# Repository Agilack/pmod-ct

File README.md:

PMOD Current Transformer
========================

This PMOD allow to interface a current transformer (CT) for current measurement
with no direct electrical coupling. This PMOD use a type 2 (SPI) port to
control the embedded 12 bits analog to digital converter.

CAD source
----------

This board has been designed using KiCad EDA (version 5). All sources files
(schematics, routing, ...) are available into the `prj-kicad` folder. You can
re-use this design under terms of the Creative Commons ShareAlike license
(CC BY-SA)

<table>
<tr>
<td></td>
<td></td>
</tr>
<tr>
<td>Fig1: Preview of the KiCad schematics</td>
<td>Fig2: Preview of the KiCad routing</td>
</tr>
</table>

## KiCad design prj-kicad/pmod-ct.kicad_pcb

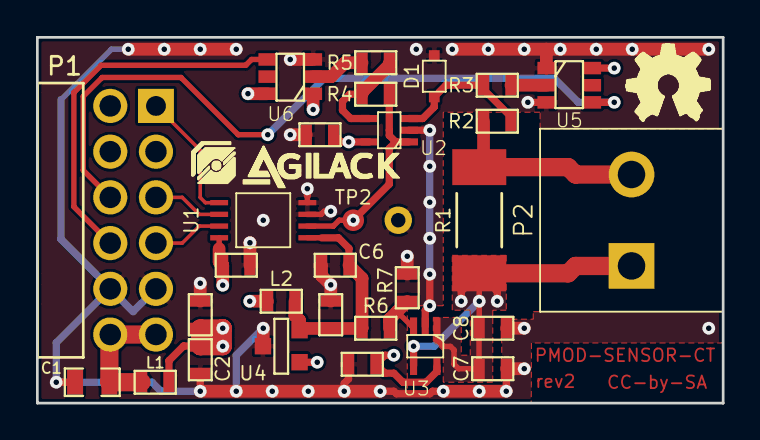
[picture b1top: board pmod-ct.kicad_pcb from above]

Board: 4 copper layers, 38.1 x 20.3 mm, 32 parts (0 on the bottom side), 17 nets.

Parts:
C1: 10uF; SMD0805
C2: 1uF; SMD0603
C3, C6, C8: 470pF; SMD0603
C4, C5, C9, C10: 100nF; SMD0603
C7: 4,7uF; SMD0603
D1: MM3Z3V3T1G; SOD323
L1, L2: FB100; SMD0603
P1: PMOD; CONN_PMOD-Male
P2: CONN_2; CONN_MC000034
R1: 33R; SMD2010
R2, R6, R7: 10k; SMD0603
R3, R4, R5: R; SMD0603
TP1: CONN_1; TP
TP2: CONN_1; TP_SMD
U1: MCP3201; MSOP-8
U2, U3: MCP6001; SC70-5
U4: REF30xx; SOT23-3
U5, U6: ADG802; SOT23-6
agilack-11.5: 450px; logo-agilack-11.5
ohw_logo: VAL**; logo-ohw

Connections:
+3.3V: C2.1, C3.1, C4.1, C5.1, C9.1, L1.2, L2.1, U1.8, U2.5, U3.5, U4.1, U5.6, U6.6
+VPMOD: C1.1, L1.1, P1.6, P1.12
+VRef: C6.1, C10.1, L2.2, R6.2, U1.1, U4.2
/VREF\2: C7.1, C8.1, P2.1, R1.2, U3.1, U3.4, U6.1
AMP: P1.10, U6.4
DIV: P1.9, U5.4
GND: C1.2, C2.2, C3.2, C4.2, C5.2, C6.2, C7.2, C8.2, C9.2, C10.2, D1.1, P1.5, P1.11, R7.1, TP1.1, U1.3, U1.4, U2.2, U3.2, U4.3, U5.1, U5.3, U6.3
unnamed: D1.2, R2.1, R3.1, U2.3
unnamed: P2.2, R1.1, R2.2
unnamed: R3.2, U5.2
unnamed: R4.1, R5.2, U2.4
unnamed: R4.2, TP2.1, U1.2, U2.1
unnamed: R5.1, U6.2
unnamed: R6.1, R7.2, U3.3
PMOD_CS: P1.1, U1.5
PMOD_MISO: P1.3, U1.6
PMOD_SCK: P1.4, U1.7

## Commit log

2020-09-08 --=={ Initial version }==-- ADD schematics and routing
2020-09-10 = ADD: Create production files
2020-09-19 = ADD: Insert picture of the board rev1
2020-10-17 Start rev2 design - Add voltage offset (VREF/2) for the burden resistor
2020-10-18 Rev2: PCB is now 4 layers ; add a switch to control input divider
2020-10-19 Rev2: Add a switch to control amplifier gain (G=1 or G=~10)

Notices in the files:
prj-kicad/pmod-ct.kicad_pcb:
License: CC-by-SA 2.0
